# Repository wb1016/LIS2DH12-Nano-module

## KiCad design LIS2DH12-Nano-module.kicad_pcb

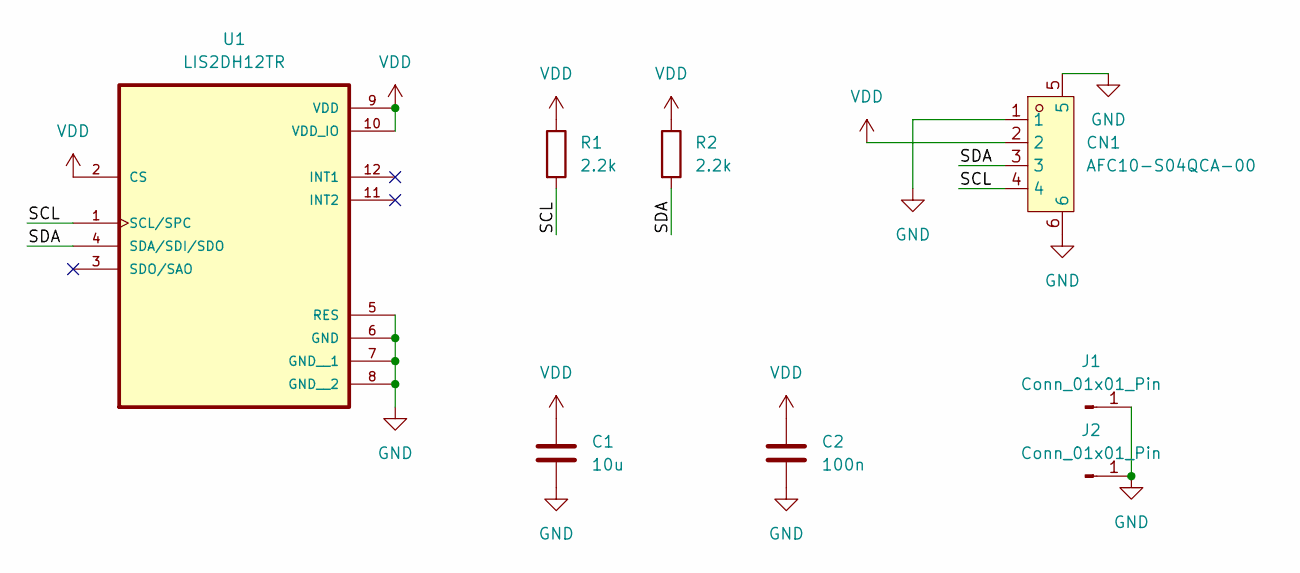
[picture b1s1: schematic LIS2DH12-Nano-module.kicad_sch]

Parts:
C1: 10u; C_0603_1608Metric
C2: 100n; C_0402_1005Metric
CN1: AFC10-S04QCA-00; CONN-SMD_AFC10-S04QCA-00; LCSC Part C2764183
J1, J2: Conn_01x01_Pin; PinHeader_1x01_P2.54mm_Vertical
R1, R2: 2.2k; R_0402_1005Metric
U1: LIS2DH12TR; LGA-12_STM

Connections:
/SCL: CN1.4, R1.2, U1.1 (SCL/SPC)
/SDA: CN1.3, R2.2, U1.4 (SDA/SDI/SDO)
GND: C1.2, C2.2, CN1.1, CN1.5, CN1.6, J1.1, J2.1, U1.5 (RES), U1.6 (GND), U1.7 (GND__1), U1.8 (GND__2)
VDD: C1.1, C2.1, CN1.2, R1.1, R2.1, U1.2 (CS), U1.9 (VDD), U1.10 (VDD_IO)

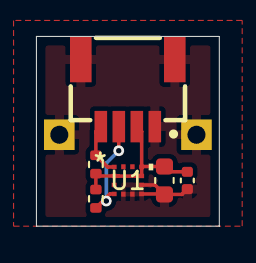
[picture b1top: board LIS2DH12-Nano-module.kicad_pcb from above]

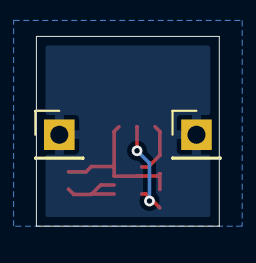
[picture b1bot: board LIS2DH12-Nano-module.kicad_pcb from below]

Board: 2 copper layers, 10.2 x 10.5 mm, 8 parts (2 on the bottom side), 4 nets.

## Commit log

2024-05-20 didnt i pushed
